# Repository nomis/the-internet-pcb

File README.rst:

The Internet PCB
================

Overview
--------

PCB to power an ESP32-C3 connected to an LED and a piezoelectric buzzer.

Dimensions: 88mm W × 40mm H

Purpose
-------

Use an ESP32-C3 in a small black rectangular plastic box (Maplin BZ74R) to make
a remotely controllable "The Internet" with a flashing red LED on top.

Include the `Wireless 3.3V Supercapacitor PCB <https://github.com/nomis/wireless-3v3-supercap-pcb>`_
for wireless power, because "The Internet" is wireless.

Place on top of `Big Ben <https://en.wikipedia.org/wiki/Big_Ben>`_ for the best
reception and don't forget to degauss it regularly.

Usage
-----

This is a KiCad project.

Schematics
----------

.. image:: render/the-internet-sch.svg
   :alt: Schematic

PCB
---

.. image:: render/the-internet-pcb.svg
   :alt: PCB

Components
----------

+---------------------+----------+--------------------------------------------------------------+
| Refs                | Quantity | Name                                                         |
+=====================+==========+==============================================================+
| J1                  |     1    | 1x06 Pin Header, Through Hole (2.54mm)                       |
+---------------------+----------+--------------------------------------------------------------+
| J2, J3              |     2    | 1x08 Pin Socket, Through Hole (2.54mm)                       |
+---------------------+----------+--------------------------------------------------------------+
| C1                  |     1    | 0.1µF Capacitor, SMD 0805 (Metric 2012)                      |
+---------------------+----------+--------------------------------------------------------------+
| D1                  |     1    | 1x02 Pin Header, Through Hole (2.54mm)                       |
|                     |     1    |                                                              |
+---------------------+----------+--------------------------------------------------------------+
| LS1                 |     1    | TDK PS1720P02 Piezo Buzzer 3V 2kHz 70dB, Through Hole (10mm) |
+---------------------+----------+--------------------------------------------------------------+
| Q1                  |     1    | ON Semiconductor KSC1815YTA NPN Transistor, TO-92-3          |
+---------------------+----------+--------------------------------------------------------------+
| R1                  |     1    | 47Ω 1% 250mW Resistor, SMD 1206 (Metric 3216)                |
+---------------------+----------+--------------------------------------------------------------+
| R2                  |     1    | 1kΩ 1% 125mW Resistor, SMD 0805 (Metric 2012)                |
+---------------------+----------+--------------------------------------------------------------+
| R3                  |     1    | 47kΩ 1% 125mW Resistor, SMD 0805 (Metric 2012)               |
+---------------------+----------+--------------------------------------------------------------+

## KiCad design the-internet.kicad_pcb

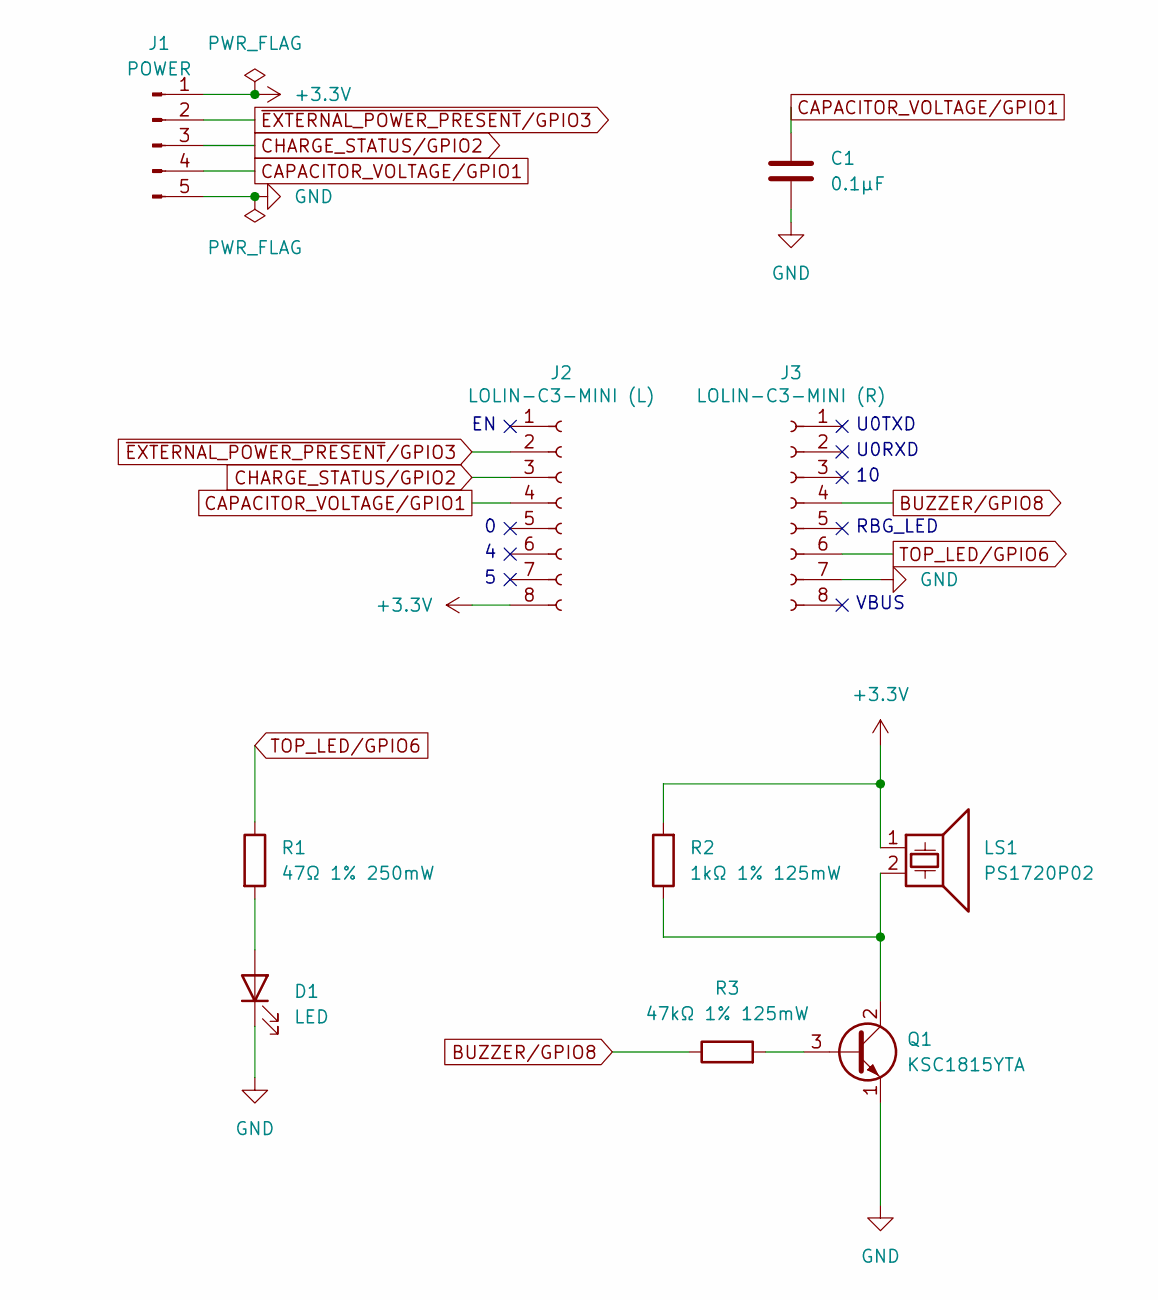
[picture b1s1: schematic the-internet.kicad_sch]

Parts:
C1: 0.1µF; C_0805_2012Metric_Pad1.18x1.45mm_HandSolder
D1: LED; PinHeader_1x02_P2.54mm_Vertical
J1: POWER; PinHeader_1x05_P2.54mm_Vertical
J2: LOLIN-C3-MINI (L); PinSocket_1x08_P2.54mm_Vertical
J3: LOLIN-C3-MINI (R); PinSocket_1x08_P2.54mm_Vertical
LS1: PS1720P02
Q1: KSC1815YTA; TO-92_Inline_Wide
R1: 47Ω 1% 250mW; R_1206_3216Metric_Pad1.30x1.75mm_HandSolder
R2: 1kΩ 1% 125mW; R_0805_2012Metric_Pad1.20x1.40mm_HandSolder
R3: 47kΩ 1% 125mW; R_0805_2012Metric_Pad1.20x1.40mm_HandSolder

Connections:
+3.3V: J1.1, J2.8, LS1.1, R2.2
BUZZER/GPIO8: J3.4, R3.1
CAPACITOR_VOLTAGE/GPIO1: C1.1, J1.4, J2.4
CHARGE_STATUS/GPIO2: J1.3, J2.3
GND: C1.2, D1.1 (K), J1.5, J3.7, Q1.1 (E)
unnamed: D1.2 (A), R1.2
unnamed: Q1.3 (B), R3.2
unnamed: LS1.2, Q1.2 (C), R2.1
TOP_LED/GPIO6: J3.6, R1.1
~EXTERNAL_POWER_PRESENT/GPIO3: J1.2, J2.2

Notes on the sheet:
U0TXD
VBUS
U0RXD
RBG_LED

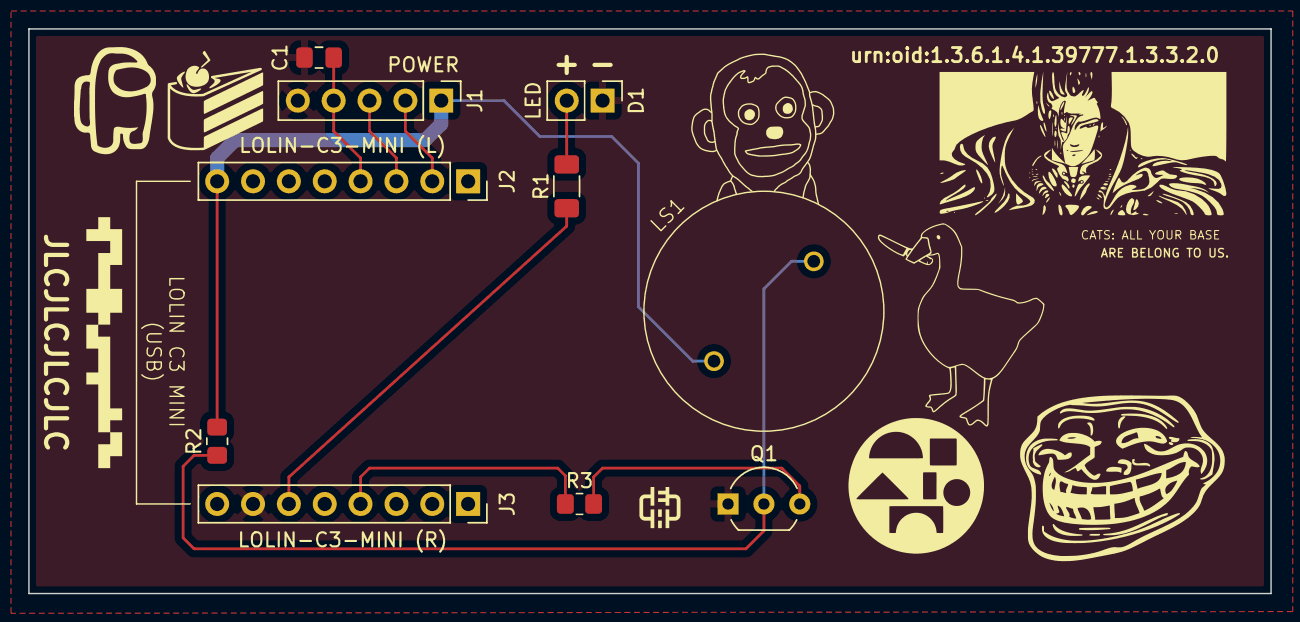
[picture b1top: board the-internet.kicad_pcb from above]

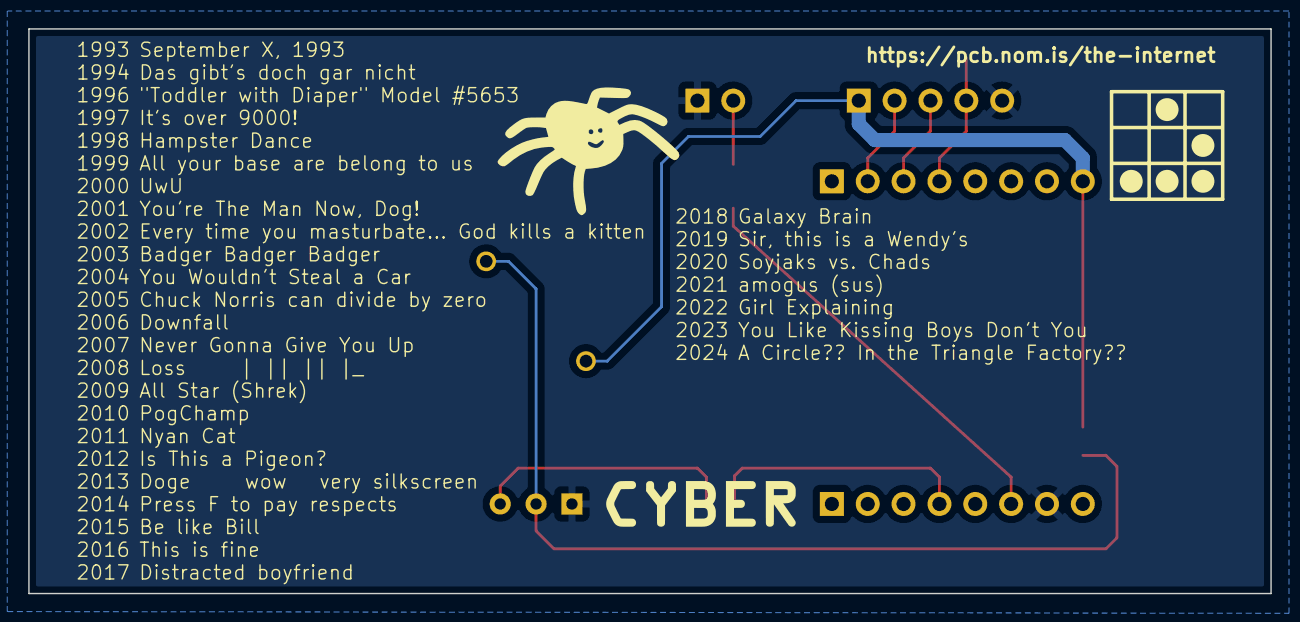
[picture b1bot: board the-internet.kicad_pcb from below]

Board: 2 copper layers, 88.0 x 40.0 mm, 22 parts (4 on the bottom side), 10 nets.

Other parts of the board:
CAKE: LOGO
CYBER: LOGO
CYBER#2: LOGO
EHLAB: LOGO
FEZ: LOGO
GOOSE: LOGO
MONKEY: LOGO
SPIDER: LOGO
SQUARE_HOLE: LOGO
SUS: LOGO
Spider: LOGO
TROLLFACE: LOGO

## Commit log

2025-07-21 Remove ADC divider control
2025-07-21 Use the better SOT-23-3 footprint for Q1, Q2
2025-07-21 Place buzzer, remove MOSFETs
2025-07-21 Add memes
2025-07-23 Move top LED to GPIO6 because GPIO10 has a glitch on powerup
2025-07-23 Add resistor to buzzer transistor
2025-07-27 Improve buzzer footprint
    Make the silkscreen circle match the buzzer itself
    Change the pad size to match the manufacturer's version
2025-07-27 Use shorter PCB URL
2025-07-27 Add JLC order number text
2025-07-27 Fit more meme years in
2025-07-27 Move JLC order number text closer to the edge
2025-07-27 Maximise space for meme text
2025-07-28 Add square hole game
2025-07-28 Add monkey
2025-07-28 Add among us character
2025-07-28 Make troll face clearer
2025-07-28 Add goose
2025-07-29 Add EH logo
2025-07-29 Add lots of other stuff
